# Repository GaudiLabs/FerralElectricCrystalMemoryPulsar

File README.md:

# FerralElectricCrystalMemoryPulsar

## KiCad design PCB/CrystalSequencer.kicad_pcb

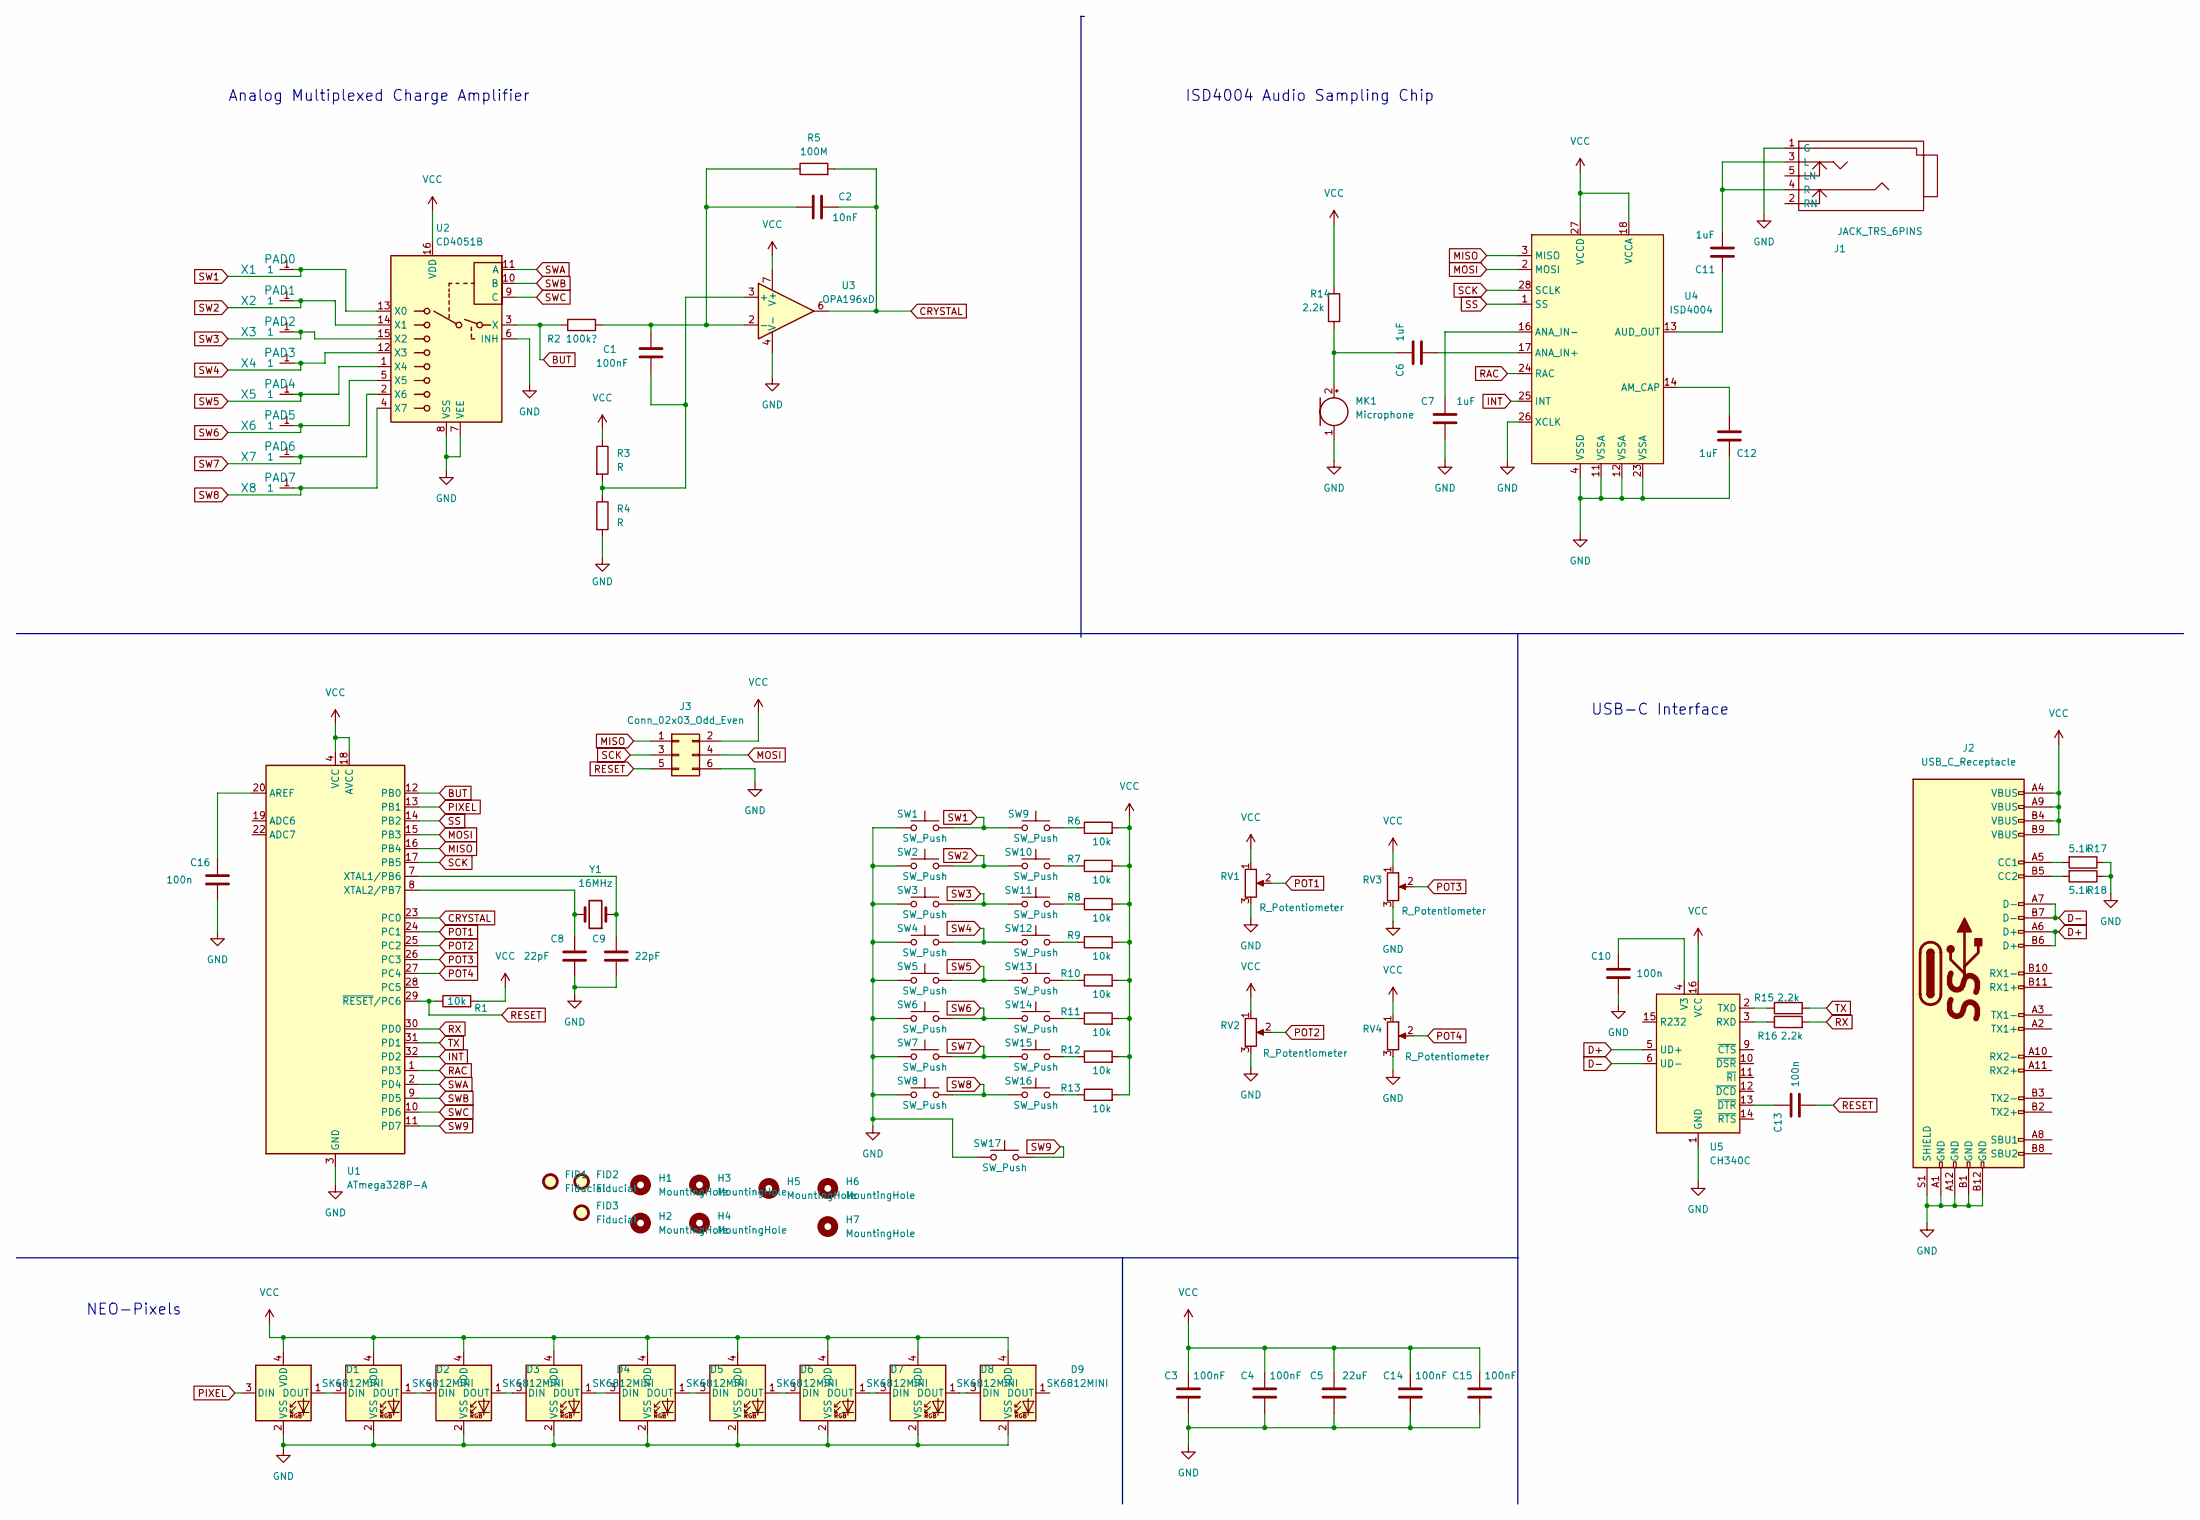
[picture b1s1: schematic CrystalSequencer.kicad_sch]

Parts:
C1, C3, C4, C14, C15: 100nF; C_0805_2012Metric
C2: 10nF; C_0805_2012Metric
C5: 22uF; C_0805_2012Metric
C6, C7, C11, C12: 1uF; C_0805_2012Metric
C8, C9: 22pF; C_0805_2012Metric
C10, C13, C16: 100n; C_0805_2012Metric
D1, D2, D3, D4, D5, D6, D7, D8, D9: SK6812MINI; LED_SK6812MINI_PLCC4_3.5x3.5mm_P1.75mm
FID1, FID2, FID3: Fiducial; Fiducial_1mm_Dia_2.54mm_Outer_CopperBottom
H1, H2, H3, H4, H5, H6, H7: MountingHole; MountingHole_3.2mm_M3
J1: JACK_TRS_6PINS; Jack3_5_Switchcraft_35RASMT4BHNTRX
J2: USB_C_Receptacle; USB_C_Receptacle_Amphenol_12401610E4-2A
J3: Conn_02x03_Odd_Even; Tag-Connect_TC2030-IDC-NL_2x03_P1.27mm_Vertical
MK1: Microphone; Zxgs-4015p Electret Microphone
R1, R6, R7, R8, R9, R10, R11, R12, R13: 10k; R_0805_2012Metric
R2: 100k?; R_0805_2012Metric
R3, R4: R; R_0805_2012Metric
R5: 100M; R_0805_2012Metric
R14, R15, R16: 2.2k; R_0805_2012Metric
R17, R18: 5.1k; R_0805_2012Metric
RV1, RV2, RV3, RV4: R_Potentiometer; POT
SW1, SW2, SW3, SW4, SW5, SW6, SW7, SW8, SW9, SW10, SW11, SW12, SW13, SW14, SW15, SW16, SW17: SW_Push; SW_SPST_TL3342
U1: ATmega328P-A; TQFP-32_7x7mm_P0.8mm
U2: CD4051B; SOIC-16_3.9x9.9mm_P1.27mm
U3: OPA196xD; SOIC-8_3.9x4.9mm_P1.27mm
U4: ISD4004; DIP-28_W15.24mm
U5: CH340C; SOIC-16_3.9x9.9mm_P1.27mm
X1: PAD0; TestPoint_THTPad_D2.5mm_Drill1.2mm
X2: PAD1; TestPoint_THTPad_D2.5mm_Drill1.2mm
X3: PAD2; TestPoint_THTPad_D2.5mm_Drill1.2mm
X4: PAD3; TestPoint_THTPad_D2.5mm_Drill1.2mm
X5: PAD4; TestPoint_THTPad_D2.5mm_Drill1.2mm
X6: PAD5; TestPoint_THTPad_D2.5mm_Drill1.2mm
X7: PAD6; TestPoint_THTPad_D2.5mm_Drill1.2mm
X8: PAD7; TestPoint_THTPad_D2.5mm_Drill1.2mm
Y1: 16MHz; Crystal_SMD_HC49-SD

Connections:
BUT: R2.1, U1.12 (PB0), U2.3 (X)
CRYSTAL: C2.2, R5.2, U1.23 (PC0), U3.6
D+: J2.A6 (D+), J2.B6 (D+), U5.5 (UD+)
D-: J2.A7 (D-), J2.B7 (D-), U5.6 (UD-)
GND: C3.1, C4.1, C5.1, C7.1, C8.1, C9.1, C10.1, C12.2, C14.1, C15.1, C16.1, D1.2 (VSS), D2.2 (VSS), D3.2 (VSS), D4.2 (VSS), D5.2 (VSS), D6.2 (VSS), D7.2 (VSS), D8.2 (VSS), D9.2 (VSS), J1.1 (G), J2.A1 (GND), J2.A12 (GND), J2.B1 (GND), J2.B12 (GND), J2.S1 (SHIELD), J3.6, MK1.1 (-), R4.2, R17.1, R18.1, RV1.3, RV2.3, RV3.3, RV4.3, SW1.1, SW2.1, SW3.1, SW4.1, SW5.1, SW6.1, SW7.1, SW8.1, SW17.1, U1.3 (GND), U1.5 (GND), U1.21 (GND), U2.6 (INH), U2.7 (VEE), U2.8 (VSS), U3.4 (V-), U4.4 (VSSD), U4.11 (VSSA), U4.12 (VSSA), U4.23 (VSSA), U4.26 (XCLK), U5.1 (GND)
INT: U1.32 (PD2), U4.25 (INT)
MISO: J3.1, U1.16 (PB4), U4.3 (MISO)
MOSI: J3.4, U1.15 (PB3), U4.2 (MOSI)
unnamed: C1.1, R3.2, R4.1, U3.3 (+)
unnamed: C1.2, C2.1, R2.2, R5.1, U3.2 (-)
unnamed: C6.1, U4.17 (ANA_IN+)
unnamed: C6.2, MK1.2 (+), R14.2
unnamed: C7.2, U4.16 (ANA_IN-)
unnamed: C8.2, U1.8 (XTAL2/PB7), Y1.2
unnamed: C9.2, U1.7 (XTAL1/PB6), Y1.1
unnamed: C10.2, U5.4 (V3)
unnamed: C11.1, J1.3 (L), J1.4 (R)
unnamed: C11.2, U4.13 (AUD_OUT)
unnamed: C12.1, U4.14 (AM_CAP)
unnamed: C13.2, U5.13 (~DTR)
unnamed: C16.2, U1.20 (AREF)
unnamed: D1.1 (DOUT), D2.3 (DIN)
unnamed: D2.1 (DOUT), D3.3 (DIN)
unnamed: D3.1 (DOUT), D4.3 (DIN)
unnamed: D4.1 (DOUT), D5.3 (DIN)
unnamed: D5.1 (DOUT), D6.3 (DIN)
unnamed: D6.1 (DOUT), D7.3 (DIN)
unnamed: D7.1 (DOUT), D8.3 (DIN)
unnamed: D8.1 (DOUT), D9.3 (DIN)
unnamed: J2.A5 (CC1), R17.2
unnamed: J2.B5 (CC2), R18.2
unnamed: R6.1, SW9.2
unnamed: R7.1, SW10.2
unnamed: R8.1, SW11.2
unnamed: R9.1, SW12.2
unnamed: R10.1, SW13.2
unnamed: R11.1, SW14.2
unnamed: R12.1, SW15.2
unnamed: R13.1, SW16.2
unnamed: R15.1, U5.2 (TXD)
unnamed: R16.1, U5.3 (RXD)
PIXEL: D1.3 (DIN), U1.13 (PB1)
POT1: RV1.2, U1.24 (PC1)
POT2: RV2.2, U1.25 (PC2)
POT3: RV3.2, U1.26 (PC3)
POT4: RV4.2, U1.27 (PC4)
RAC: U1.1 (PD3), U4.24 (RAC)
RESET: C13.1, J3.5, R1.1, U1.29 (~RESET/PC6)
RX: R16.2, U1.30 (PD0)
SCK: J3.3, U1.17 (PB5), U4.28 (SCLK)
SS: U1.14 (PB2), U4.1 (SS)
SW1: SW1.2, SW9.1, U2.13 (X0), X1.1
SW2: SW2.2, SW10.1, U2.14 (X1), X2.1
SW3: SW3.2, SW11.1, U2.15 (X2), X3.1
SW4: SW4.2, SW12.1, U2.12 (X3), X4.1
SW5: SW5.2, SW13.1, U2.1 (X4), X5.1
SW6: SW6.2, SW14.1, U2.5 (X5), X6.1
SW7: SW7.2, SW15.1, U2.2 (X6), X7.1
SW8: SW8.2, SW16.1, U2.4 (X7), X8.1
SW9: SW17.2, U1.11 (PD7)
SWA: U1.2 (PD4), U2.11 (A)
SWB: U1.9 (PD5), U2.10 (B)
SWC: U1.10 (PD6), U2.9 (C)
TX: R15.2, U1.31 (PD1)
VCC: C3.2, C4.2, C5.2, C14.2, C15.2, D1.4 (VDD), D2.4 (VDD), D3.4 (VDD), D4.4 (VDD), D5.4 (VDD), D6.4 (VDD), D7.4 (VDD), D8.4 (VDD), D9.4 (VDD), J2.A4 (VBUS), J2.A9 (VBUS), J2.B4 (VBUS), J2.B9 (VBUS), J3.2, R1.2, R3.1, R6.2, R7.2, R8.2, R9.2, R10.2, R11.2, R12.2, R13.2, R14.1, RV1.1, RV2.1, RV3.1, RV4.1, U1.4 (VCC), U1.6 (VCC), U1.18 (AVCC), U2.16 (VDD), U3.7 (V+), U4.18 (VCCA), U4.27 (VCCD), U5.16 (VCC)

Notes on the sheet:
Analog Multiplexed Charge Amplifier
NEO-Pixels
ISD4004 Audio Sampling Chip
USB-C Interface

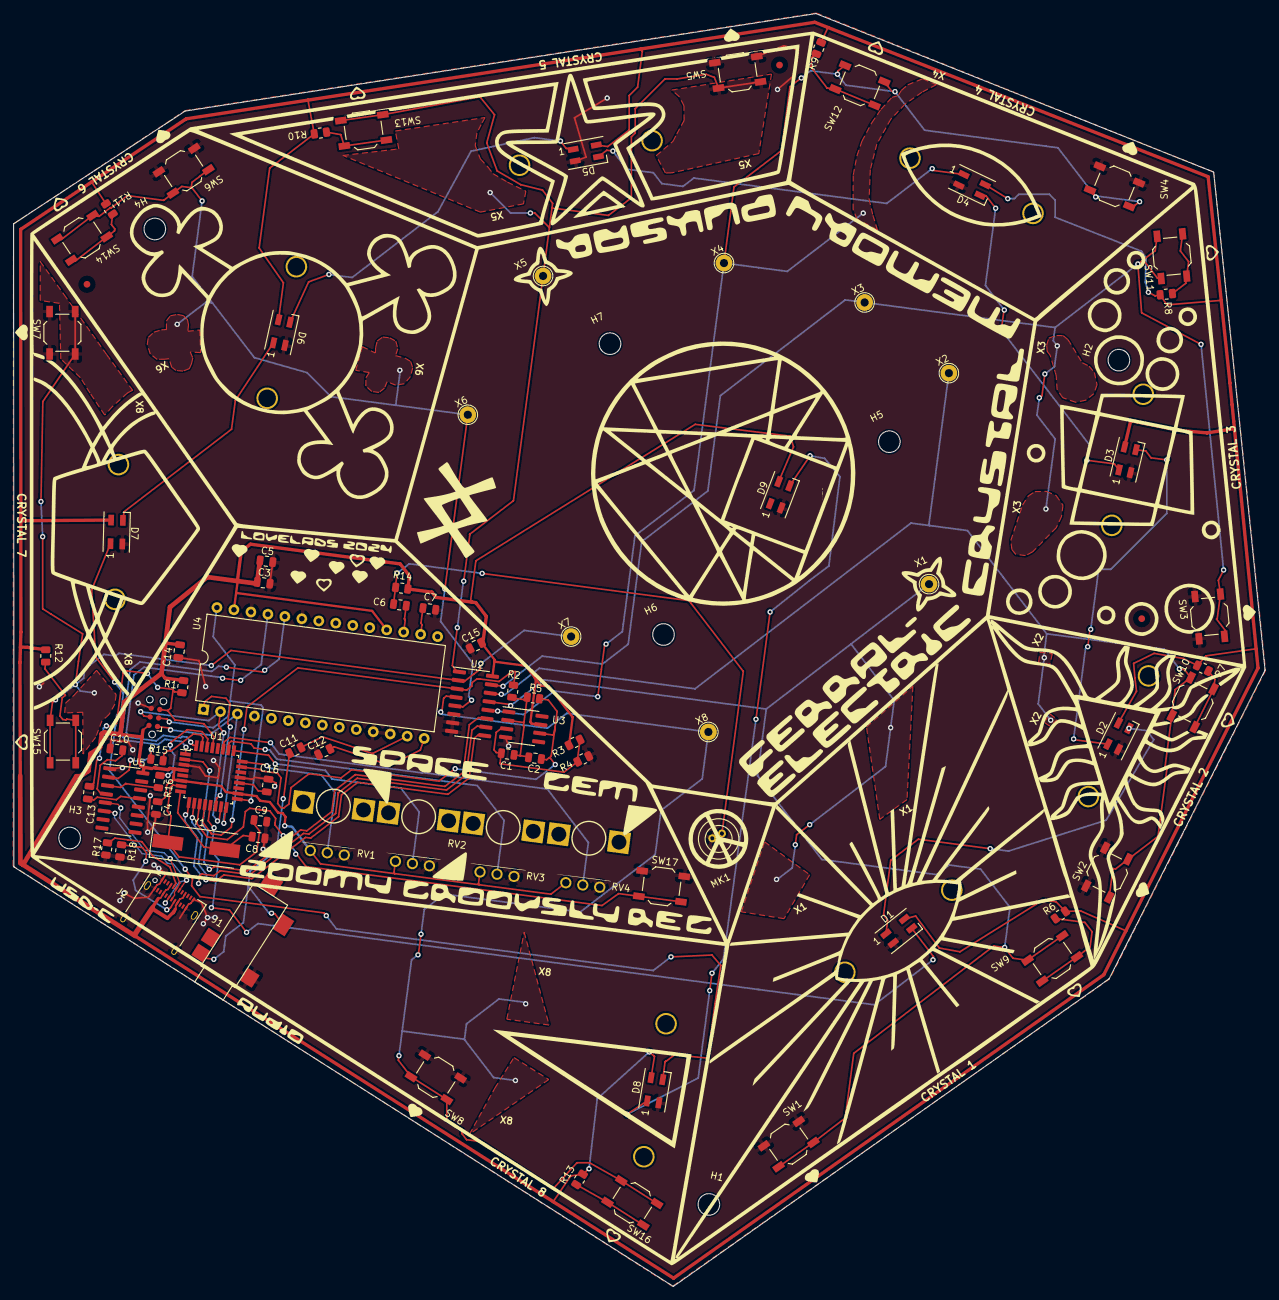
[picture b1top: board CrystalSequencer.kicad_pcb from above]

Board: 2 copper layers, 185.7 x 188.8 mm, 92 parts (0 on the bottom side), 65 nets.

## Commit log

2024-02-01 First Design Big one
2024-02-09 Sent to PCB manuafcruting Yeah
